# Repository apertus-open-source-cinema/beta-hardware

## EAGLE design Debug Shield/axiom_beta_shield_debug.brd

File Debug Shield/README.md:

# AXIOM Beta Debug Shield v0.2

https://wiki.apertus.org/index.php/Beta_Debug_Shield

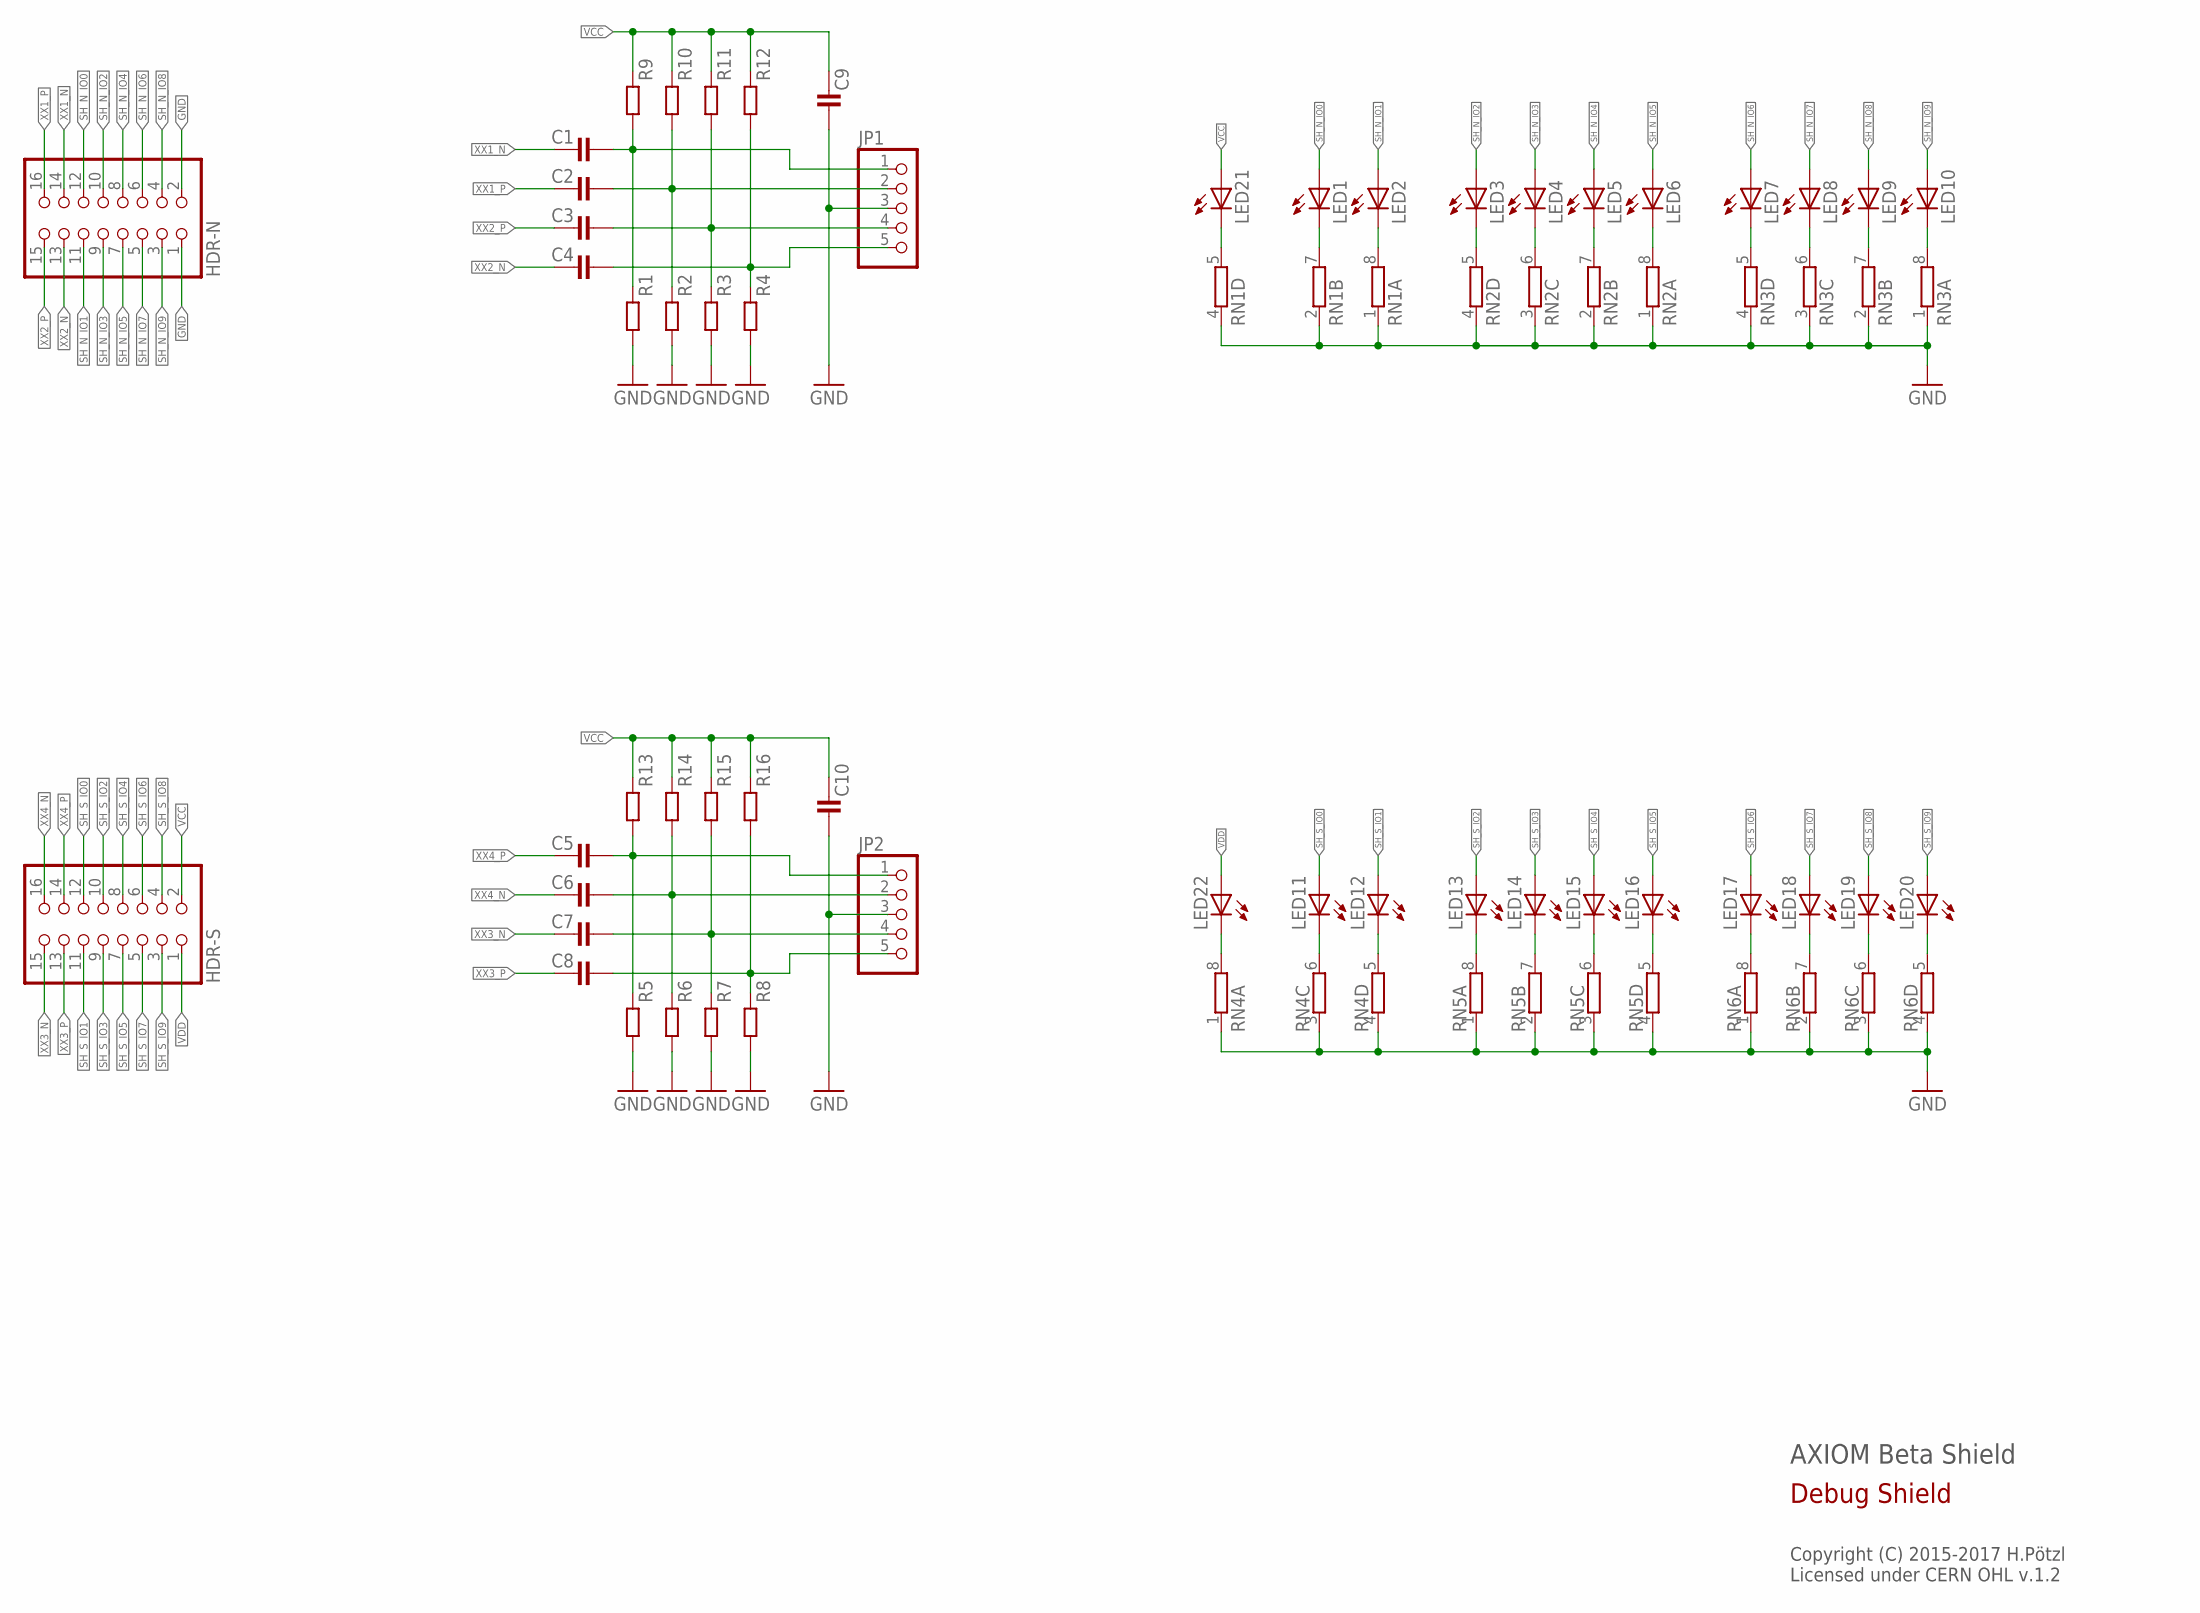
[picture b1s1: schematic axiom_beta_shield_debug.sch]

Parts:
C1, C2, C3, C4, C5, C6, C7, C8: C0402-C; 0402-C
C9, C10: C0805-C; 0805-C
HDR-N: PINHD-2X08_2.00_SMD; 2X08M_SMD
HDR-S: PINHD-2X08_2.00_SMD; 2X08M_SMD
JP1, JP2: PINHD-1X05_1.27; 1X05U
LED1, LED2, LED3, LED4, LED5, LED6, LED7, LED8, LED9, LED10, LED11, LED12, LED13, LED14, LED15, LED16, LED17, LED18, LED19, LED20, LED21, LED22: LEDCHIPLED_0603; CHIPLED_0603
R1, R2, R3, R4, R5, R6, R7, R8, R9, R10, R11, R12, R13, R14, R15, R16: R0402-C; 0402-C
RN1, RN2, RN3, RN4, RN5, RN6: 4R-NCAY16; CAY16

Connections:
GND: C9.2, C10.2, HDR-N.1, HDR-N.2, JP1.3, JP2.3, R1.2, R2.2, R3.2, R4.2, R5.2, R6.2, R7.2, R8.2, RN1.1, RN1.2 (1), RN1.4 (1), RN2.1, RN2.2 (1), RN2.3 (1), RN2.4 (1), RN3.1, RN3.2 (1), RN3.3 (1), RN3.4 (1), RN4.1, RN4.3 (1), RN4.4 (1), RN5.1, RN5.2 (1), RN5.3 (1), RN5.4 (1), RN6.1, RN6.2 (1), RN6.3 (1), RN6.4 (1)
unnamed: LED20.C, RN6.5 (2)
unnamed: LED19.C, RN6.6 (2)
unnamed: LED18.C, RN6.7 (2)
unnamed: LED17.C, RN6.8 (2)
unnamed: LED16.C, RN5.5 (2)
unnamed: LED15.C, RN5.6 (2)
unnamed: LED14.C, RN5.7 (2)
unnamed: LED13.C, RN5.8 (2)
unnamed: LED12.C, RN4.5 (2)
unnamed: LED11.C, RN4.6 (2)
unnamed: LED3.C, RN2.5 (2)
unnamed: LED4.C, RN2.6 (2)
unnamed: LED5.C, RN2.7 (2)
unnamed: LED6.C, RN2.8 (2)
unnamed: LED7.C, RN3.5 (2)
unnamed: LED8.C, RN3.6 (2)
unnamed: LED9.C, RN3.7 (2)
unnamed: LED10.C, RN3.8 (2)
unnamed: LED1.C, RN1.7 (2)
unnamed: LED2.C, RN1.8 (2)
unnamed: C1.2, JP1.1, R1.1, R9.2
unnamed: C2.2, JP1.2, R2.1, R10.2
unnamed: C3.2, JP1.4, R3.1, R11.2
unnamed: C4.2, JP1.5, R4.1, R12.2
unnamed: C5.2, JP2.1, R5.1, R13.2
unnamed: C6.2, JP2.2, R6.1, R14.2
unnamed: LED21.C, RN1.5 (2)
unnamed: C7.2, JP2.4, R7.1, R15.2
unnamed: C8.2, JP2.5, R8.1, R16.2
unnamed: LED22.C, RN4.8 (2)
SH_N_IO0: HDR-N.12, LED1.A
SH_N_IO1: HDR-N.11, LED2.A
SH_N_IO2: HDR-N.10, LED3.A
SH_N_IO3: HDR-N.9, LED4.A
SH_N_IO4: HDR-N.8, LED5.A
SH_N_IO5: HDR-N.7, LED6.A
SH_N_IO6: HDR-N.6, LED7.A
SH_N_IO7: HDR-N.5, LED8.A
SH_N_IO8: HDR-N.4, LED9.A
SH_N_IO9: HDR-N.3, LED10.A
SH_S_IO0: HDR-S.12, LED11.A
SH_S_IO1: HDR-S.11, LED12.A
SH_S_IO2: HDR-S.10, LED13.A
SH_S_IO3: HDR-S.9, LED14.A
SH_S_IO4: HDR-S.8, LED15.A
SH_S_IO5: HDR-S.7, LED16.A
SH_S_IO6: HDR-S.6, LED17.A
SH_S_IO7: HDR-S.5, LED18.A
SH_S_IO8: HDR-S.4, LED19.A
SH_S_IO9: HDR-S.3, LED20.A
VCC: C9.1, C10.1, HDR-S.2, LED21.A, R9.1, R10.1, R11.1, R12.1, R13.1, R14.1, R15.1, R16.1
VDD: HDR-S.1, LED22.A
XX1_N: C1.1, HDR-N.14
XX1_P: C2.1, HDR-N.16
XX2_N: C4.1, HDR-N.13
XX2_P: C3.1, HDR-N.15
XX3_N: C7.1, HDR-S.15
XX3_P: C8.1, HDR-S.13
XX4_N: C6.1, HDR-S.16
XX4_P: C5.1, HDR-S.14

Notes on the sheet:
AXIOM Beta Shield
Copyright (C) 2015-2017 H.Pötzl Licensed under CERN OHL v.1.2
Debug Shield

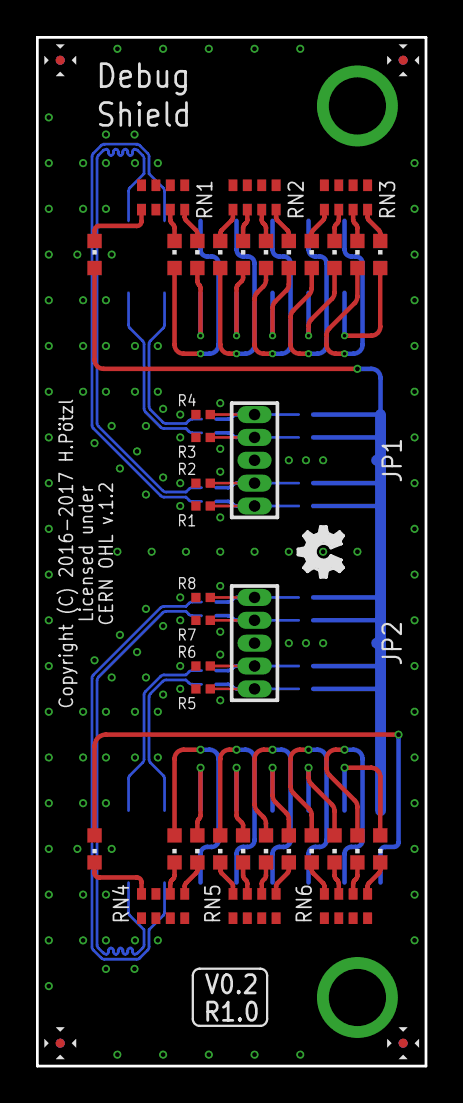
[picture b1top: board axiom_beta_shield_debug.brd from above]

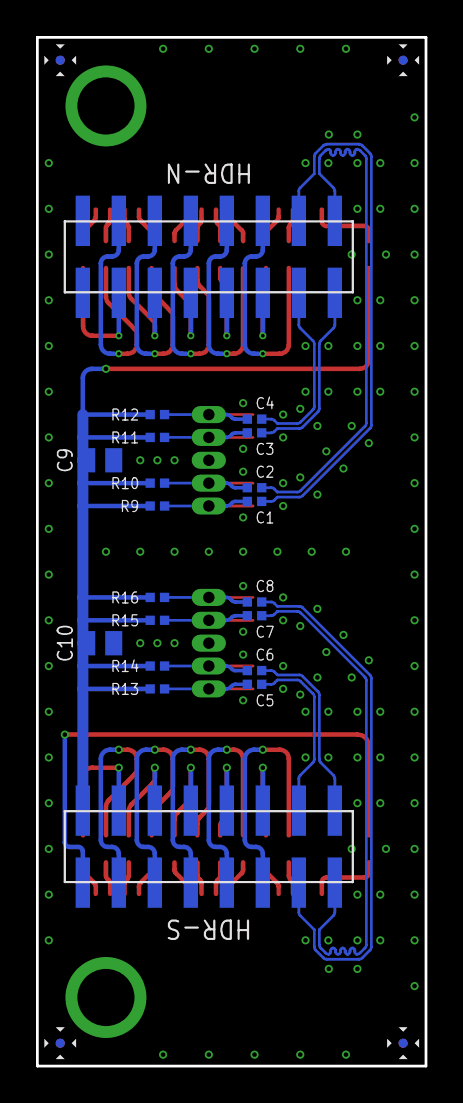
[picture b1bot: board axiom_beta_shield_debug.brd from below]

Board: 4 copper layers, 21.6 x 57.1 mm, 59 parts (20 on the bottom side), 61 nets.

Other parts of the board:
LOGO1: OSHW_LOGO_FILLX0100-NT; OSHW_FILLX100_NOTEXT

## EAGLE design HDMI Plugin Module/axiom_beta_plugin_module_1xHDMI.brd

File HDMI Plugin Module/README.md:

# AXIOM Beta 1x HDMI Plugin Module v0.8

https://wiki.apertus.org/index.php/Beta_HDMI_Plugin_Module

## Bill Of Materials

You find the BOM on [Octopart](https://octopart.com/bom-lookup/hmYtWrqZ) or [Google Docs](https://docs.google.com/spreadsheets/d/1rfcWiGjYmpbNHJG1RbKr23s07RdtV5YKcEwW8YpzaAQ/edit?usp=sharing).

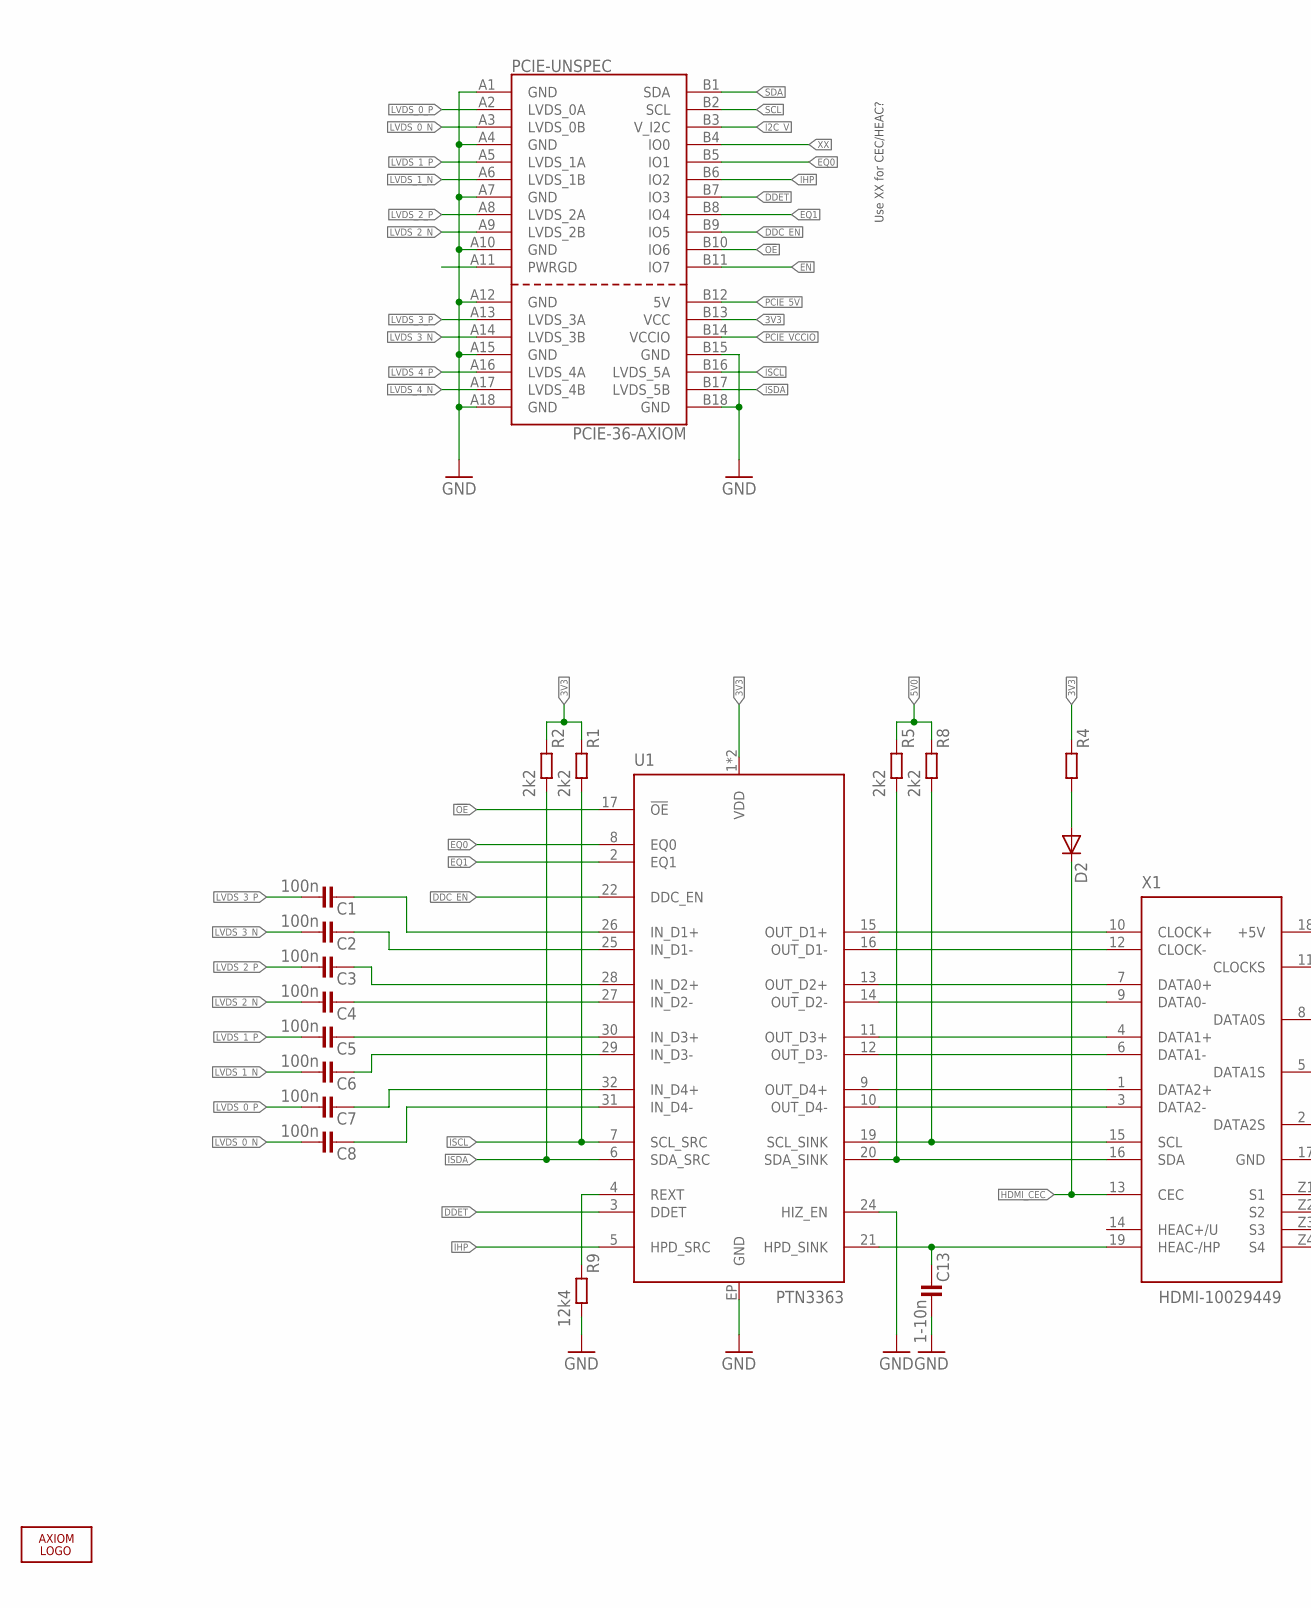
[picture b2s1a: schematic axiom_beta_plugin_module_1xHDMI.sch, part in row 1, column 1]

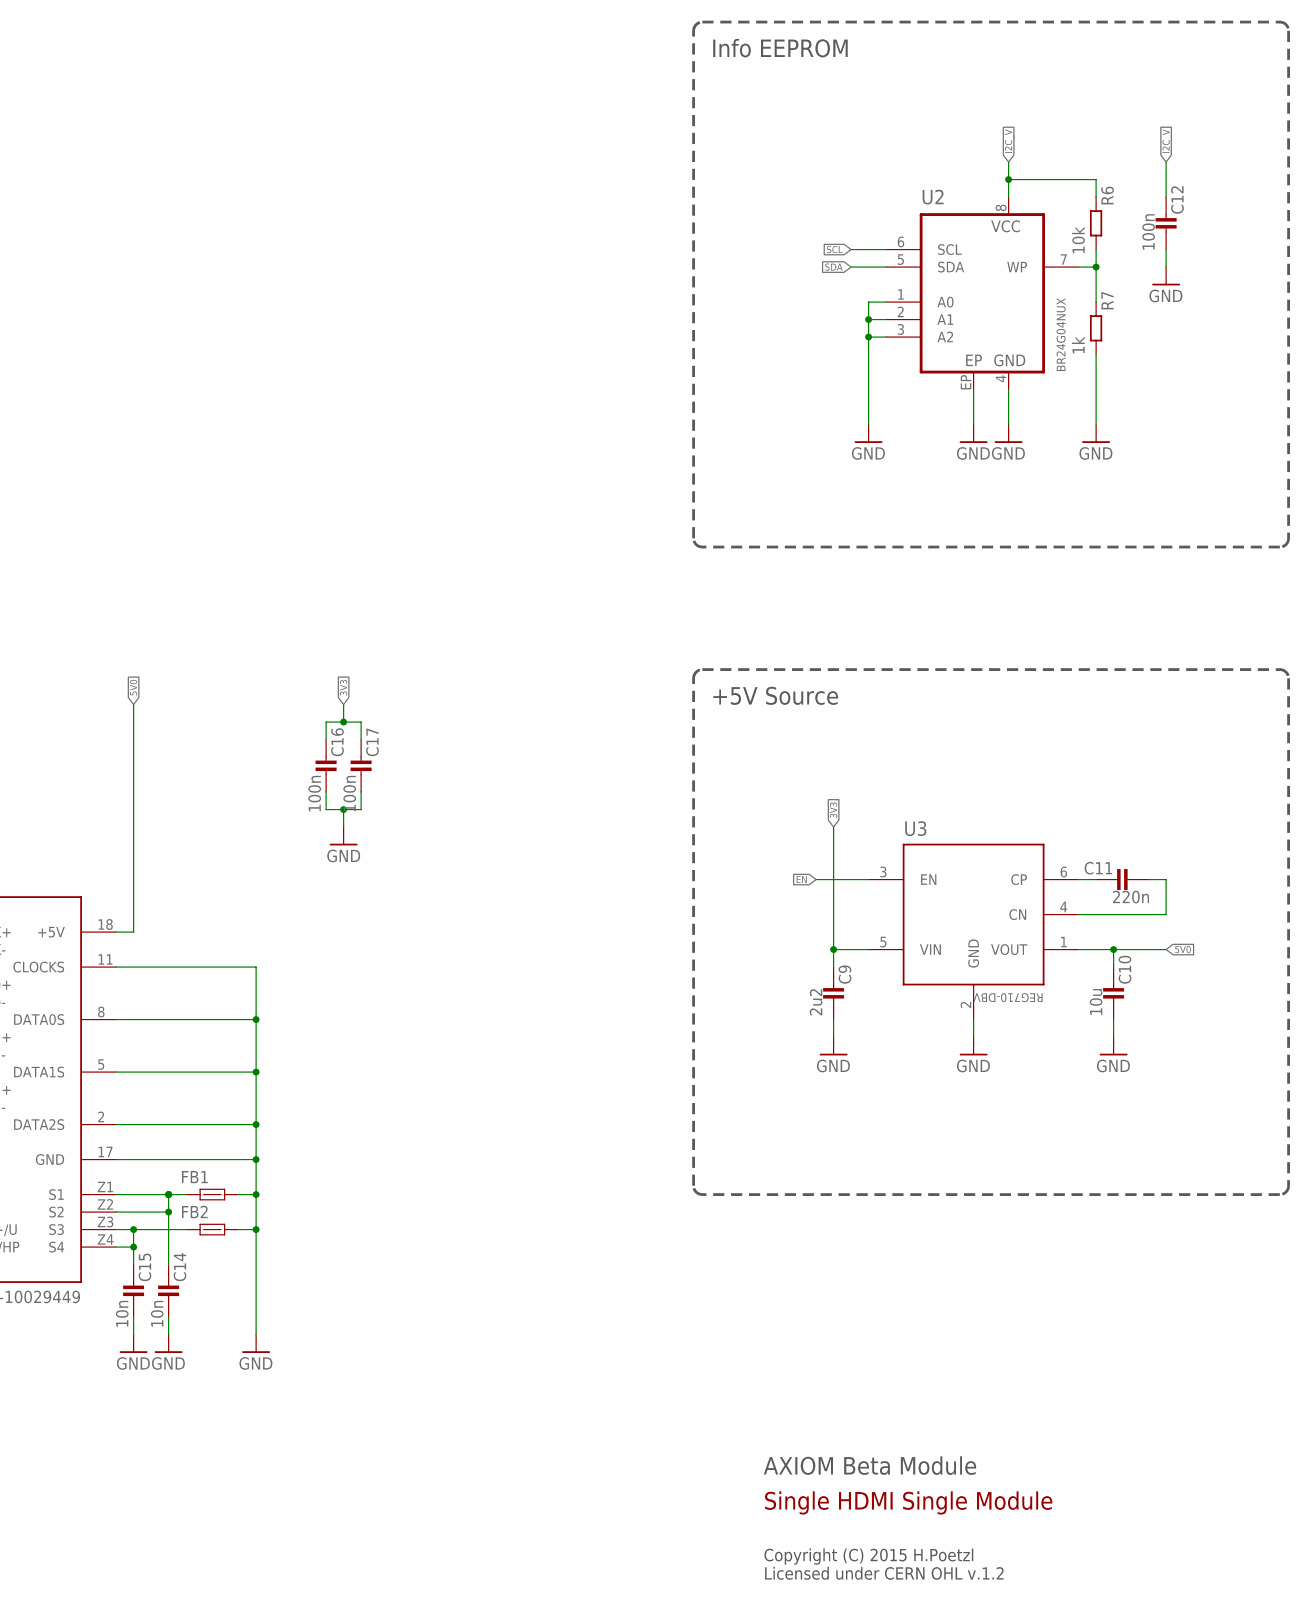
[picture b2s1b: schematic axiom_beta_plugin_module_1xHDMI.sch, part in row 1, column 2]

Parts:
C1, C2, C3, C4, C5, C6, C7, C8: 100n; 0402-C
C9: 2u2; 0603-B
C10: 10u; 0603-B
C11: 220n; 0603-B
C12, C16, C17: 100n; 0402-B
C13: 1-10n; 0402-B
C14, C15: 10n; 0402-B
D2: DIODE-SOD523; SOD523
FB1, FB2: FB0603-B; 0603-B
PCIE-UNSPEC: PCIE-36-AXIOM
R1, R2, R5, R8: 2k2; 0402-B
R4: R0402-B; 0402-B
R6: 10k; 0402-B
R7: 1k; 0402-B
R9: 12k4; 0402-B
U1: PTN3363; HVQFN32
U2: BR24G04NUX; DFN200X300X100-9N
U3: REG710-DBV; DBV
U$1: AXIOM_LOGO459X70; AXIOM_LOGO_459X70
X1: HDMI-10029449; 10029449-X01XLF

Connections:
3V3: C9.1, C16.1, C17.1, PCIE-UNSPEC.B13 (VCC), R1.1, R2.1, R4.1, U1.1 (VDD), U1.18 (VDD), U3.5 (VIN)
5V0: C10.1, R5.1, R8.1, U3.1 (VOUT), X1.18 (+5V)
!OE!: PCIE-UNSPEC.B10 (IO6), U1.17 (!OE!)
CLOCK_N: U1.16 (OUT_D1-), X1.12 (CLOCK-)
CLOCK_P: U1.15 (OUT_D1+), X1.10 (CLOCK+)
DATA0_N: U1.14 (OUT_D2-), X1.9 (DATA0-)
DATA0_P: U1.13 (OUT_D2+), X1.7 (DATA0+)
DATA1_N: U1.12 (OUT_D3-), X1.6 (DATA1-)
DATA1_P: U1.11 (OUT_D3+), X1.4 (DATA1+)
DATA2_N: U1.10 (OUT_D4-), X1.3 (DATA2-)
DATA2_P: U1.9 (OUT_D4+), X1.1 (DATA2+)
DDC_EN: PCIE-UNSPEC.B9 (IO5), U1.22 (DDC_EN)
DDET: PCIE-UNSPEC.B7 (IO3), U1.3 (DDET)
EN: PCIE-UNSPEC.B11 (IO7), U3.3 (EN)
EQ0: PCIE-UNSPEC.B5 (IO1), U1.8 (EQ0)
EQ1: PCIE-UNSPEC.B8 (IO4), U1.2 (EQ1)
GND: C9.2, C10.2, C12.2, C13.2, C14.2, C15.2, C16.2, C17.2, FB1.2, FB2.2, PCIE-UNSPEC.A1 (GND), PCIE-UNSPEC.A4 (GND), PCIE-UNSPEC.A7 (GND), PCIE-UNSPEC.A10 (GND), PCIE-UNSPEC.A12 (GND), PCIE-UNSPEC.A15 (GND), PCIE-UNSPEC.A18 (GND), PCIE-UNSPEC.B15 (GND), PCIE-UNSPEC.B18 (GND), R7.2, R9.2, U1.24 (HIZ_EN), U1.EP (GND), U2.1 (A0), U2.2 (A1), U2.3 (A2), U2.4 (GND), U2.EP, U3.2 (GND), X1.2 (DATA2S), X1.5 (DATA1S), X1.8 (DATA0S), X1.11 (CLOCKS), X1.17 (GND)
HDMI_CEC: D2.C, X1.13 (CEC)
HDMI_HP: C13.1, U1.21 (HPD_SINK), X1.19 (HEAC-/HP)
HDMI_SCL: R8.2, U1.19 (SCL_SINK), X1.15 (SCL)
HDMI_SDA: R5.2, U1.20 (SDA_SINK), X1.16 (SDA)
I2C_V: C12.1, PCIE-UNSPEC.B3 (V_I2C), R6.1, U2.8 (VCC)
IHP: PCIE-UNSPEC.B6 (IO2), U1.5 (HPD_SRC)
IN_D1_N: C2.1, U1.25 (IN_D1-)
IN_D1_P: C1.1, U1.26 (IN_D1+)
IN_D2_N: C4.1, U1.27 (IN_D2-)
IN_D2_P: C3.1, U1.28 (IN_D2+)
IN_D3_N: C6.1, U1.29 (IN_D3-)
IN_D3_P: C5.1, U1.30 (IN_D3+)
IN_D4_N: C8.1, U1.31 (IN_D4-)
IN_D4_P: C7.1, U1.32 (IN_D4+)
ISCL: PCIE-UNSPEC.B16 (LVDS_5A), R1.2, U1.7 (SCL_SRC)
ISDA: PCIE-UNSPEC.B17 (LVDS_5B), R2.2, U1.6 (SDA_SRC)
LVDS_0_N: C8.2, PCIE-UNSPEC.A3 (LVDS_0B)
LVDS_0_P: C7.2, PCIE-UNSPEC.A2 (LVDS_0A)
LVDS_1_N: C6.2, PCIE-UNSPEC.A6 (LVDS_1B)
LVDS_1_P: C5.2, PCIE-UNSPEC.A5 (LVDS_1A)
LVDS_2_N: C4.2, PCIE-UNSPEC.A9 (LVDS_2B)
LVDS_2_P: C3.2, PCIE-UNSPEC.A8 (LVDS_2A)
LVDS_3_N: C2.2, PCIE-UNSPEC.A14 (LVDS_3B)
LVDS_3_P: C1.2, PCIE-UNSPEC.A13 (LVDS_3A)
LVDS_4_N: PCIE-UNSPEC.A17 (LVDS_4B)
LVDS_4_P: PCIE-UNSPEC.A16 (LVDS_4A)
unnamed: C11.1, U3.6 (CP)
unnamed: C11.2, U3.4 (CN)
unnamed: C14.1, FB1.1, X1.Z1 (S1), X1.Z2 (S2)
unnamed: R6.2, R7.1, U2.7 (WP)
unnamed: C15.1, FB2.1, X1.Z3 (S3), X1.Z4 (S4)
unnamed: R9.1, U1.4 (REXT)
unnamed: D2.A, R4.2
PCIE_5V: PCIE-UNSPEC.B12 (5V)
PCIE_VCCIO: PCIE-UNSPEC.B14 (VCCIO)
SCL: PCIE-UNSPEC.B2 (SCL), U2.6 (SCL)
SDA: PCIE-UNSPEC.B1 (SDA), U2.5 (SDA)
XX: PCIE-UNSPEC.B4 (IO0)

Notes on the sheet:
AXIOM Beta Module
Copyright (C) 2015 H.Poetzl Licensed under CERN OHL v.1.2
Single HDMI Single Module
Info EEPROM
+5V Source
Use XX for CEC/HEAC?

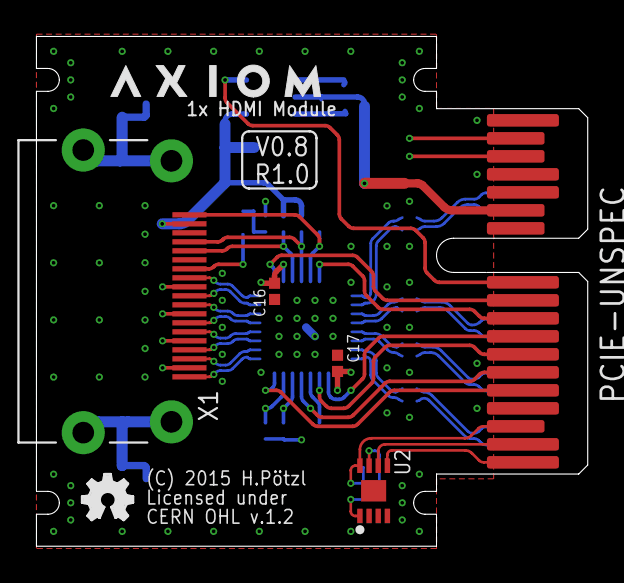
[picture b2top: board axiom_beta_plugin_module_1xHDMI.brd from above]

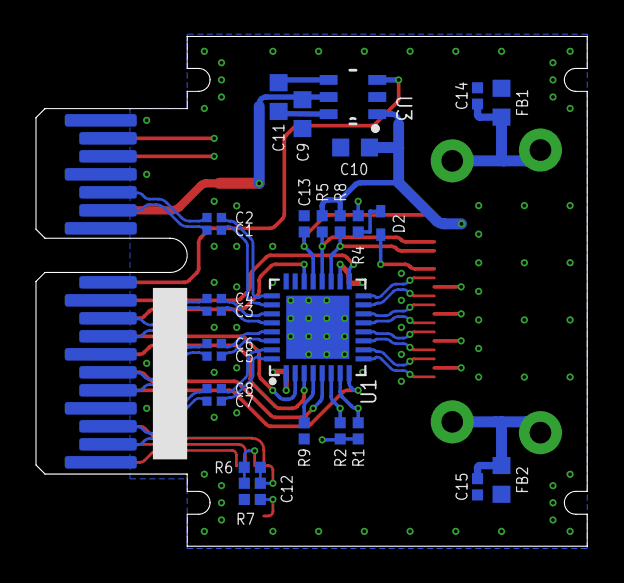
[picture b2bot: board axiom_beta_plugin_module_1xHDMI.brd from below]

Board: 4 copper layers, 30.6 x 28.3 mm, 35 parts (28 on the bottom side), 50 nets.

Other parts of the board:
LOGO2: OSHW_LOGO_FILLX0100-NT; OSHW_FILLX100_NOTEXT

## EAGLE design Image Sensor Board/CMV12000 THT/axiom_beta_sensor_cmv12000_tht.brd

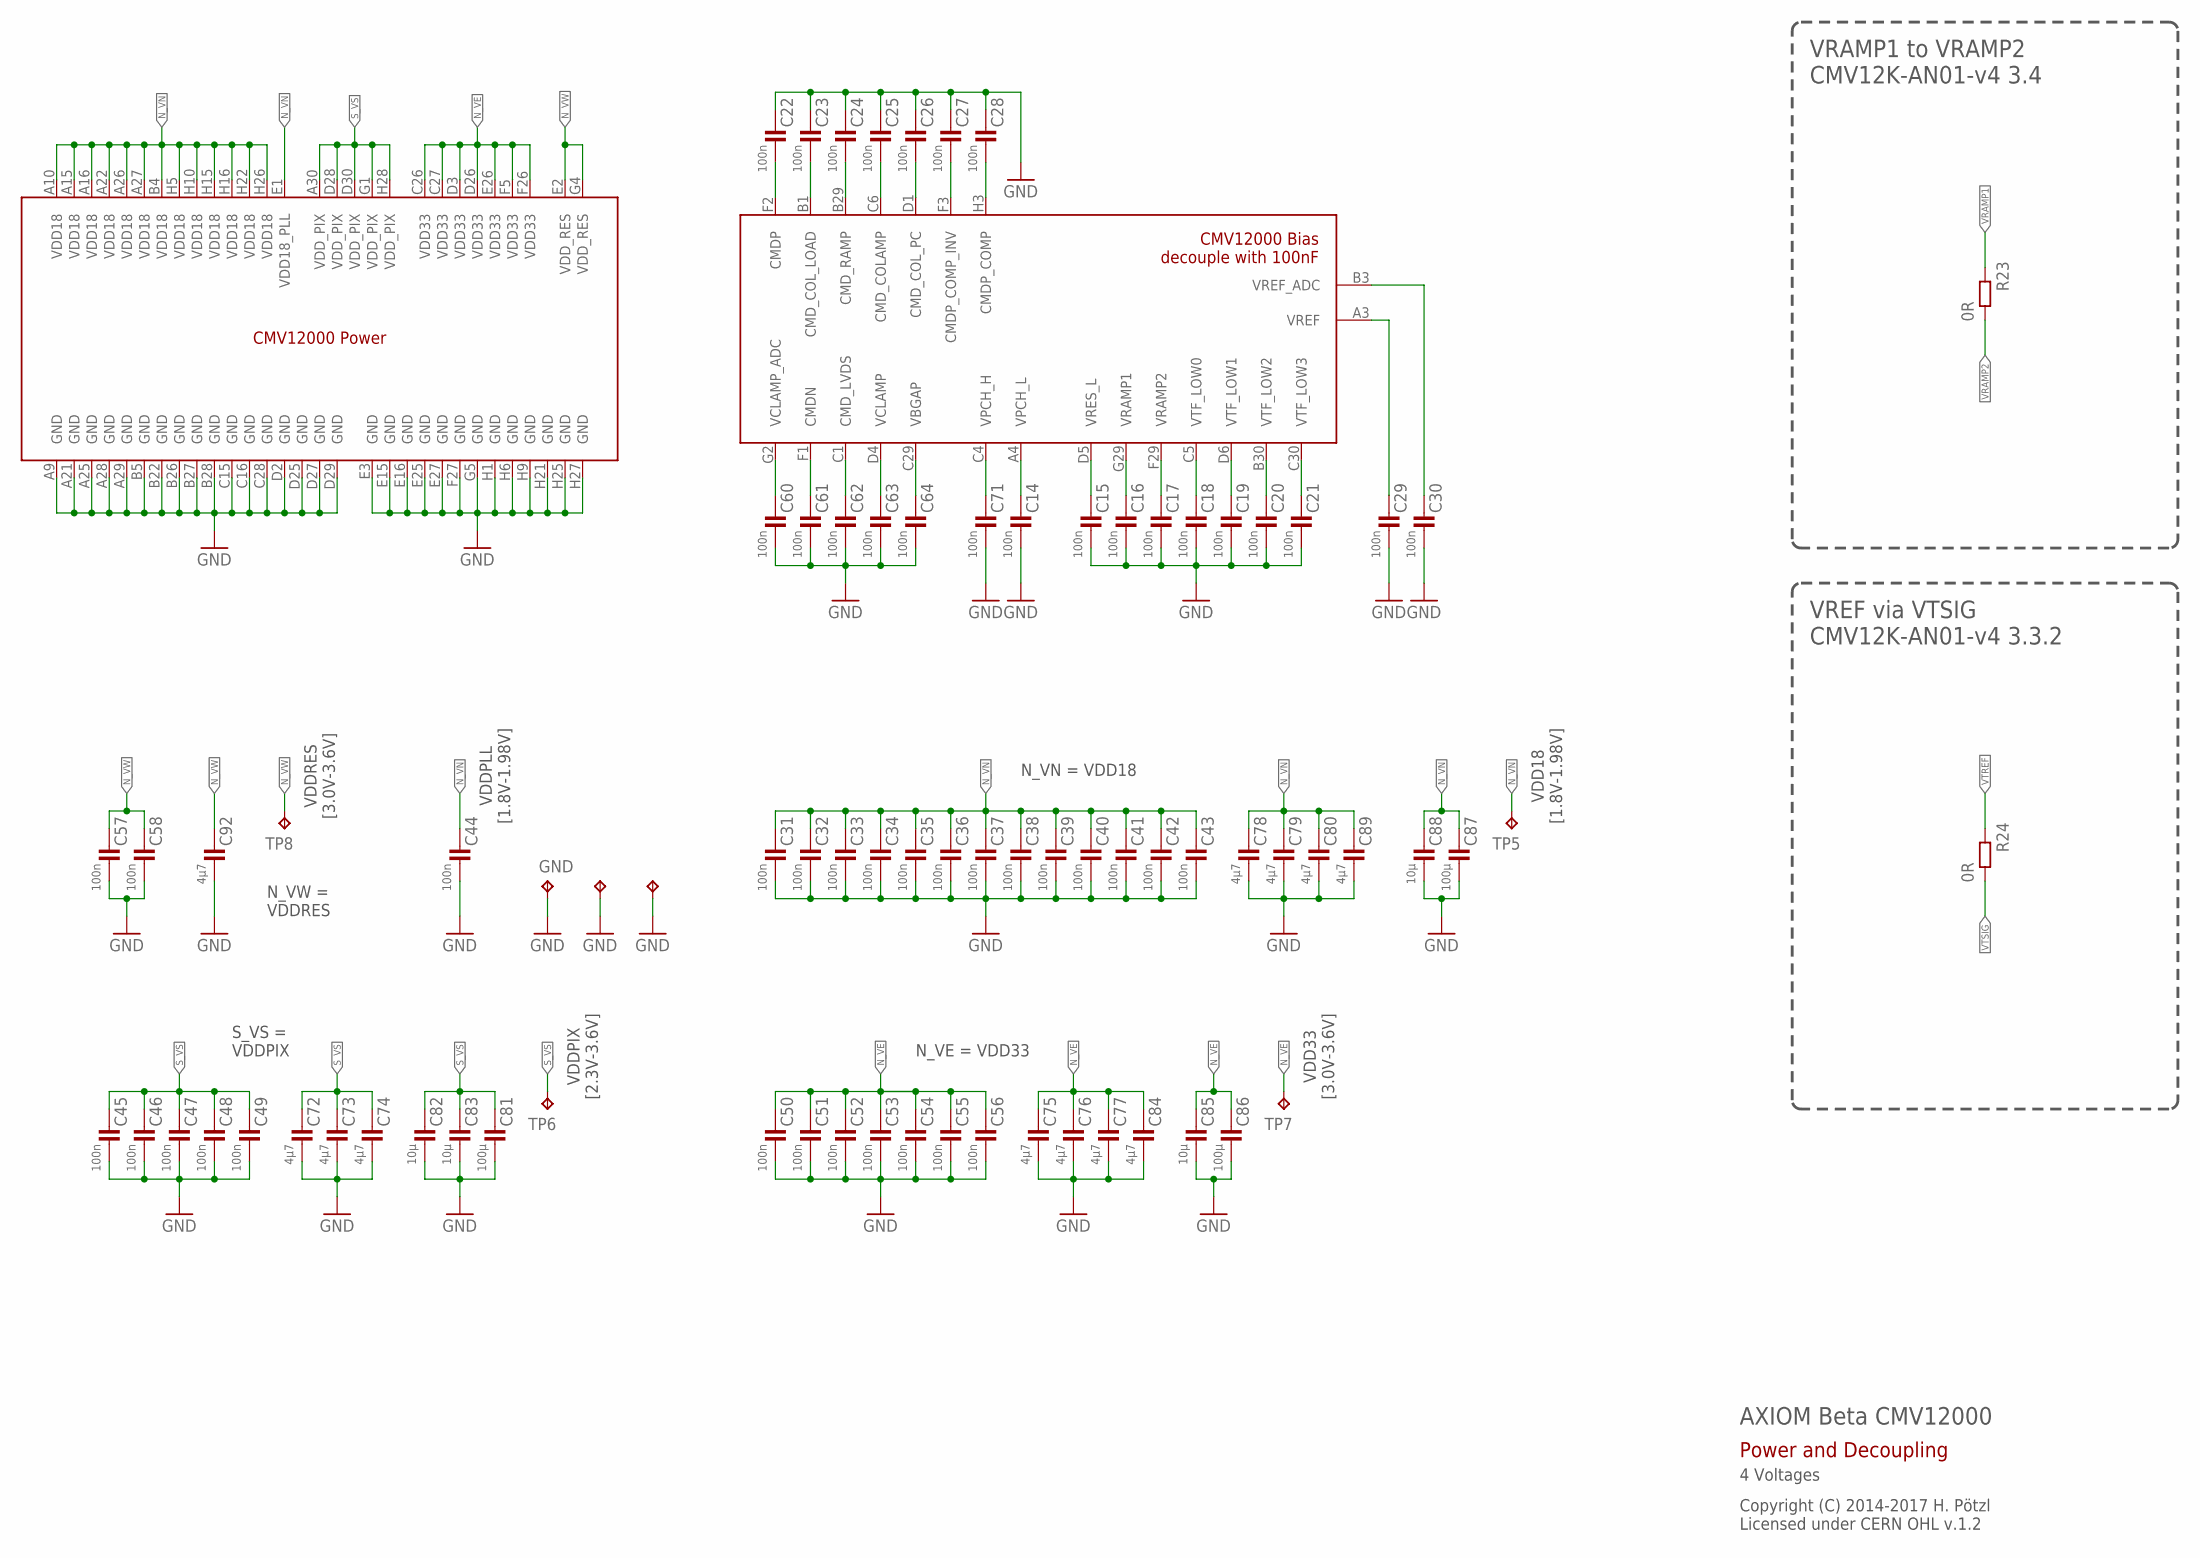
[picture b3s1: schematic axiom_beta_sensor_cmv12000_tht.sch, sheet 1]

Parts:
C14, C15, C16, C17, C18, C19, C20, C21, C22, C23, C24, C25, C26, C27, C28, C29, C30, C31, C32, C33, C34, C35, C36, C37, C38, C39, C40, C41, C42, C43, C44, C45, C46, C47, C48, C49, C50, C51, C52, C53, C54, C55, C56, C57, C58, C60, C61, C62, C63, C64, C71: 100n; 0402-C
C72, C77, C78: 4µ7; 0402-B
C73, C74, C75, C76, C79, C80, C84, C89, C92: 4µ7; 0402-C
C81, C86, C87: 100µ; 1206-B
C82, C83, C85, C88: 10µ; 0603-C
GND, GND75, GND77: TPTP10R; TP10R
R23, R24: 0R; 0402-C
SENSOR: CMV12000ANDON-CREAM; 10-30-07-237-400T4-CREAM
TP5, TP6, TP7, TP8: TPTP10R; TP10R

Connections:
GND: C14.2, C15.2, C16.2, C17.2, C18.2, C19.2, C20.2, C21.2, C22.1, C23.1, C24.1, C25.1, C26.1, C27.1, C28.1, C29.2, C30.2, C31.2, C32.2, C33.2, C34.2, C35.2, C36.2, C37.2, C38.2, C39.2, C40.2, C41.2, C42.2, C43.2, C44.2, C45.2, C46.2, C47.2, C48.2, C49.2, C50.2, C51.2, C52.2, C53.2, C54.2, C55.2, C56.2, C57.2, C58.2, C60.2, C61.2, C62.2, C63.2, C64.2, C71.2, C72.2, C73.2, C74.2, C75.2, C76.2, C77.2, C78.2, C79.2, C80.2, C81.2, C82.2, C83.2, C84.2, C85.2, C86.2, C87.2, C88.2, C89.2, C92.2, GND.TP, GND75.TP, GND77.TP, SENSOR.A9 (GND), SENSOR.A21 (GND), SENSOR.A25 (GND), SENSOR.A28 (GND), SENSOR.A29 (GND), SENSOR.B5 (GND), SENSOR.B22 (GND), SENSOR.B26 (GND), SENSOR.B27 (GND), SENSOR.B28 (GND), SENSOR.C15 (GND), SENSOR.C16 (GND), SENSOR.C28 (GND), SENSOR.D2 (GND), SENSOR.D25 (GND), SENSOR.D27 (GND), SENSOR.D29 (GND), SENSOR.E3 (GND), SENSOR.E15 (GND), SENSOR.E16 (GND), SENSOR.E25 (GND), SENSOR.E27 (GND), SENSOR.F27 (GND), SENSOR.G5 (GND), SENSOR.H1 (GND), SENSOR.H6 (GND), SENSOR.H9 (GND), SENSOR.H21 (GND), SENSOR.H25 (GND), SENSOR.H27 (GND); also elsewhere on the board
unnamed: C60.1, SENSOR.G2 (VCLAMP_ADC)
unnamed: C61.1, SENSOR.F1 (CMDN)
unnamed: C62.1, SENSOR.C1 (CMD_LVDS)
unnamed: C63.1, SENSOR.D4 (VCLAMP)
unnamed: C64.1, SENSOR.C29 (VBGAP)
unnamed: C71.1, SENSOR.C4 (VPCH_H)
unnamed: C14.1, SENSOR.A4 (VPCH_L)
unnamed: C15.1, SENSOR.D5 (VRES_L)
unnamed: C18.1, SENSOR.C5 (VTF_LOW0)
unnamed: C19.1, SENSOR.D6 (VTF_LOW1)
unnamed: C20.1, SENSOR.B30 (VTF_LOW2)
unnamed: C21.1, SENSOR.C30 (VTF_LOW3)
unnamed: C22.2, SENSOR.F2 (CMDP)
unnamed: C23.2, SENSOR.B1 (CMD_COL_LOAD)
unnamed: C24.2, SENSOR.B29 (CMD_RAMP)
unnamed: C25.2, SENSOR.C6 (CMD_COLAMP)
unnamed: C26.2, SENSOR.D1 (CMD_COL_PC)
unnamed: C27.2, SENSOR.F3 (CMDP_COMP_INV)
unnamed: C28.2, SENSOR.H3 (CMDP_COMP)
unnamed: C29.1, SENSOR.A3 (VREF)
unnamed: C30.1, SENSOR.B3 (VREF_ADC)
N_VE: C50.1, C51.1, C52.1, C53.1, C54.1, C55.1, C56.1, C75.1, C76.1, C77.1, C84.1, C85.1, C86.1, SENSOR.C26 (VDD33), SENSOR.C27 (VDD33), SENSOR.D3 (VDD33), SENSOR.D26 (VDD33), SENSOR.E26 (VDD33), SENSOR.F5 (VDD33), SENSOR.F26 (VDD33), TP7.TP; also elsewhere on the board
N_VN: C31.1, C32.1, C33.1, C34.1, C35.1, C36.1, C37.1, C38.1, C39.1, C40.1, C41.1, C42.1, C43.1, C44.1, C78.1, C79.1, C80.1, C87.1, C88.1, C89.1, SENSOR.A10 (VDD18), SENSOR.A15 (VDD18), SENSOR.A16 (VDD18), SENSOR.A22 (VDD18), SENSOR.A26 (VDD18), SENSOR.A27 (VDD18), SENSOR.B4 (VDD18), SENSOR.E1 (VDD18_PLL), SENSOR.H5 (VDD18), SENSOR.H10 (VDD18), SENSOR.H15 (VDD18), SENSOR.H16 (VDD18), SENSOR.H22 (VDD18), SENSOR.H26 (VDD18), TP5.TP; also elsewhere on the board
N_VW: C57.1, C58.1, C92.1, SENSOR.E2 (VDD_RES), SENSOR.G4 (VDD_RES), TP8.TP; also elsewhere on the board
S_VS: C45.1, C46.1, C47.1, C48.1, C49.1, C72.1, C73.1, C74.1, C81.1, C82.1, C83.1, SENSOR.A30 (VDD_PIX), SENSOR.D28 (VDD_PIX), SENSOR.D30 (VDD_PIX), SENSOR.G1 (VDD_PIX), SENSOR.H28 (VDD_PIX), TP6.TP; also elsewhere on the board
VRAMP1: C16.1, R23.1, SENSOR.G29 (VRAMP1)
VRAMP2: C17.1, R23.2, SENSOR.F29 (VRAMP2)
VTREF: R24.1; also elsewhere on the board
VTSIG: R24.2; also elsewhere on the board

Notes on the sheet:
N_VN = VDD18
N_VE = VDD33
VDDPIX [2.3V-3.6V]
VDDRES [3.0V-3.6V]
VREF via VTSIG CMV12K-AN01-v4 3.3.2
VRAMP1 to VRAMP2 CMV12K-AN01-v4 3.4
AXIOM Beta CMV12000
Copyright (C) 2014-2017 H. Pötzl Licensed under CERN OHL v.1.2
Power and Decoupling
4 Voltages
VDD18 [1.8V-1.98V]
VDD33 [3.0V-3.6V]
VDDPLL [1.8V-1.98V]
S_VS = VDDPIX
N_VW = VDDRES

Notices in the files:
Debug Shield/axiom_beta_shield_debug.brd:
Copyright (C) 2016-2017 H.Pötzl
Licensed under
CERN OHL v.1.2
HDMI Plugin Module/axiom_beta_plugin_module_1xHDMI.brd:
(C) 2015 H.Pötzl
PCBs/axiom_beta_main_board_v0.36_r1.2/axiom_beta_main_board_v0.36_r1.2.brd:
Copyright (C) 2015-2016 Herbert Pötzl
PCBs/axiom_beta_power_board_v0.37_r1.2/axiom_beta_power_board_v0.37_r1.2.brd:
Copyright (C) 2015-2020 H.Pötzl
PMOD Plugin Module/axiom_beta_plugin_module_1xPMOD.brd:
Copyright (C) 2016 Herbert Pötzl
